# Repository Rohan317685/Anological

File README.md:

# Analogical 

This is Analogical; a project I've made for chipless.hackclub.com, The main goal of this project was to learn analog and not use a microcontroller! 

It is a 6 node transistor only signal network where each block drives, perturbs and destabalises the next creating a really chaotic annalog behaviour which cannot be replicated with a MCU

| Item                             | Item description                | Quantity | Price   | Link                                                                                                  |
|----------------------------------|---------------------------------|----------|---------|-------------------------------------------------------------------------------------------------------|
| PCB                              | Printed Circuit Board           | 5        | $5.5    | https://jlcpcb.com/                                                                                   |
| 10uF capacitor                   | for the led transistor          | 20       | $1.16   | https://www.lcsc.com/product-detail/C669099.html                                                      |
| 100nF capacitor                  | For decoupling                  | 50       | $1.07   | https://www.lcsc.com/product-detail/C89258.html                                                       |
| 10uF Electrolytic Capacitor      | For decoupling                  | 50       | $ 1.05  | https://www.lcsc.com/product-detail/C2841113.html                                                     |
| Red LED                          | For showing the patterns        | 20       | $ 0.73  | https://www.lcsc.com/product-detail/Light-Emitting-Diodes-LED_red_C99772.html                         |
| 1n41482 diode                    | For reverse polarity protection | 5        | $0.73   | https://www.lcsc.com/product-detail/C112342.html |
|  Pin header 1x2                  | For power supply                | 20        | $ 0.61  | https://www.lcsc.com/product-detail/C124375.html                                                      |
| Transistor JSCJ C1815 120~240-TA | For the transistors ofc         | 40       | $  1.04 | https://www.lcsc.com/product-detail/C382004.html                                                      |
| Resistor 100k                    | For resisting                   | 100      | $0.29   | https://www.lcsc.com/product-detail/C416061.html                                                      |
| Resistor 1k                      | For resisting aswell            | 100      | $ 0.42  | https://www.lcsc.com/product-detail/Chip-Resistor-Surface-Mount_1KR-1000-1_C95781.html                |
| AMS1117-3.3                      | Voltage regulator               | 5        | $ 0.99  | https://www.lcsc.com/product-detail/C6186.html                                                        |
|LCSC fees                         |Shipping/handling fees           | N/A      |$7.89    | lcsc.com                                                                                              |

I have used the cheapest shipping options and it comes to a total off: $22.48

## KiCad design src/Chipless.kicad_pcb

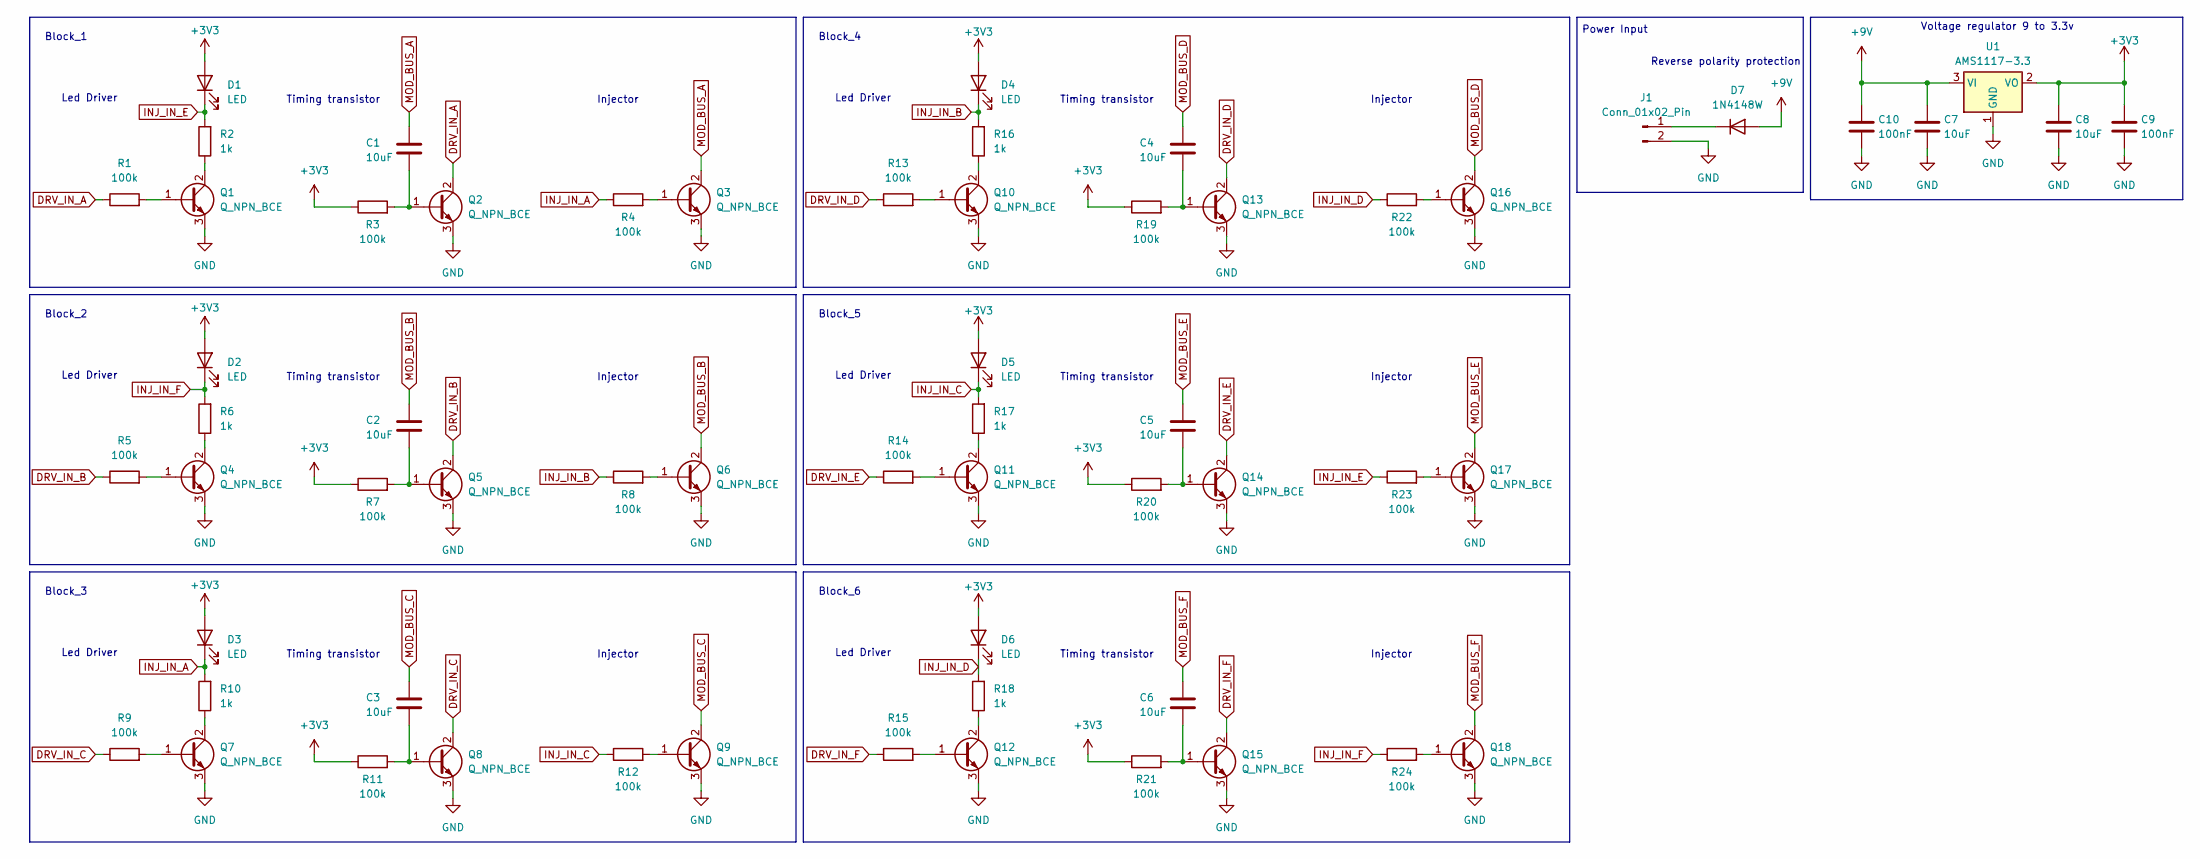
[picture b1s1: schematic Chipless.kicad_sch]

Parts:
C1, C2, C3, C4, C5, C6: 10uF; C_0805_2012Metric
C7, C8: 10uF; CP_Radial_D5.0mm_P2.00mm
C9, C10: 100nF; C_0805_2012Metric
D1, D2, D3, D4, D5, D6: LED; LED_D3.0mm
D7: 1N4148W; D_SOD-123
J1: Conn_01x02_Pin; PinHeader_1x02_P2.54mm_Vertical
Q1, Q2, Q3, Q4, Q5, Q6, Q7, Q8, Q9, Q10, Q11, Q12, Q13, Q14, Q15, Q16, Q17, Q18: Q_NPN_BCE; TO-92_Inline
R1, R3, R4, R5, R7, R8, R9, R11, R12, R13, R14, R15, R19, R20, R21, R22, R23, R24: 100k; R_0805_2012Metric
R2, R6, R10, R16, R17, R18: 1k; R_0805_2012Metric
U1: AMS1117-3.3; SOT-223-3_TabPin2

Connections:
+3V3: C8.1, C9.1, D1.2 (A), D2.2 (A), D3.2 (A), D4.2 (A), D5.2 (A), D6.2 (A), R3.1, R7.1, R11.1, R19.1, R20.1, R21.1, U1.2 (VO)
+9V: C7.1, C10.1, D7.2 (A), U1.3 (VI)
DRV_IN_A: Q2.2 (C), R1.1
DRV_IN_B: Q5.2 (C), R5.1
DRV_IN_C: Q8.2 (C), R9.1
DRV_IN_D: Q13.2 (C), R13.1
DRV_IN_E: Q14.2 (C), R14.1
DRV_IN_F: Q15.2 (C), R15.1
GND: C7.2, C8.2, C9.2, C10.2, J1.2, Q1.3 (E), Q2.3 (E), Q3.3 (E), Q4.3 (E), Q5.3 (E), Q6.3 (E), Q7.3 (E), Q8.3 (E), Q9.3 (E), Q10.3 (E), Q11.3 (E), Q12.3 (E), Q13.3 (E), Q14.3 (E), Q15.3 (E), Q16.3 (E), Q17.3 (E), Q18.3 (E), U1.1 (GND)
INJ_IN_A: D3.1 (K), R4.1, R10.2
INJ_IN_B: D4.1 (K), R8.1, R16.2
INJ_IN_C: D5.1 (K), R12.1, R17.2
INJ_IN_D: D6.1 (K), R18.2, R22.1
INJ_IN_E: D1.1 (K), R2.2, R23.1
INJ_IN_F: D2.1 (K), R6.2, R24.1
MOD_BUS_A: C1.1, Q3.2 (C)
MOD_BUS_B: C2.1, Q6.2 (C)
MOD_BUS_C: C3.1, Q9.2 (C)
MOD_BUS_D: C4.1, Q16.2 (C)
MOD_BUS_E: C5.1, Q17.2 (C)
MOD_BUS_F: C6.1, Q18.2 (C)
unnamed: D7.1 (K), J1.1
unnamed: Q1.1 (B), R1.2
unnamed: Q1.2 (C), R2.1
unnamed: C1.2, Q2.1 (B), R3.2
unnamed: Q3.1 (B), R4.2
unnamed: Q4.1 (B), R5.2
unnamed: Q4.2 (C), R6.1
unnamed: C2.2, Q5.1 (B), R7.2
unnamed: Q6.1 (B), R8.2
unnamed: Q7.1 (B), R9.2
unnamed: Q7.2 (C), R10.1
unnamed: C3.2, Q8.1 (B), R11.2
unnamed: Q9.1 (B), R12.2
unnamed: Q10.1 (B), R13.2
unnamed: Q10.2 (C), R16.1
unnamed: Q11.1 (B), R14.2
unnamed: Q11.2 (C), R17.1
unnamed: Q12.1 (B), R15.2
unnamed: Q12.2 (C), R18.1
unnamed: C4.2, Q13.1 (B), R19.2
unnamed: C5.2, Q14.1 (B), R20.2
unnamed: C6.2, Q15.1 (B), R21.2
unnamed: Q16.1 (B), R22.2
unnamed: Q17.1 (B), R23.2
unnamed: Q18.1 (B), R24.2

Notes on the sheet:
Led Driver
Block_3
Reverse polarity protection
Block_6
Voltage regulator 9 to 3.3v
Power Input
Timing transistor
Block_2
Injector
Block_1
Block_5
Block_4

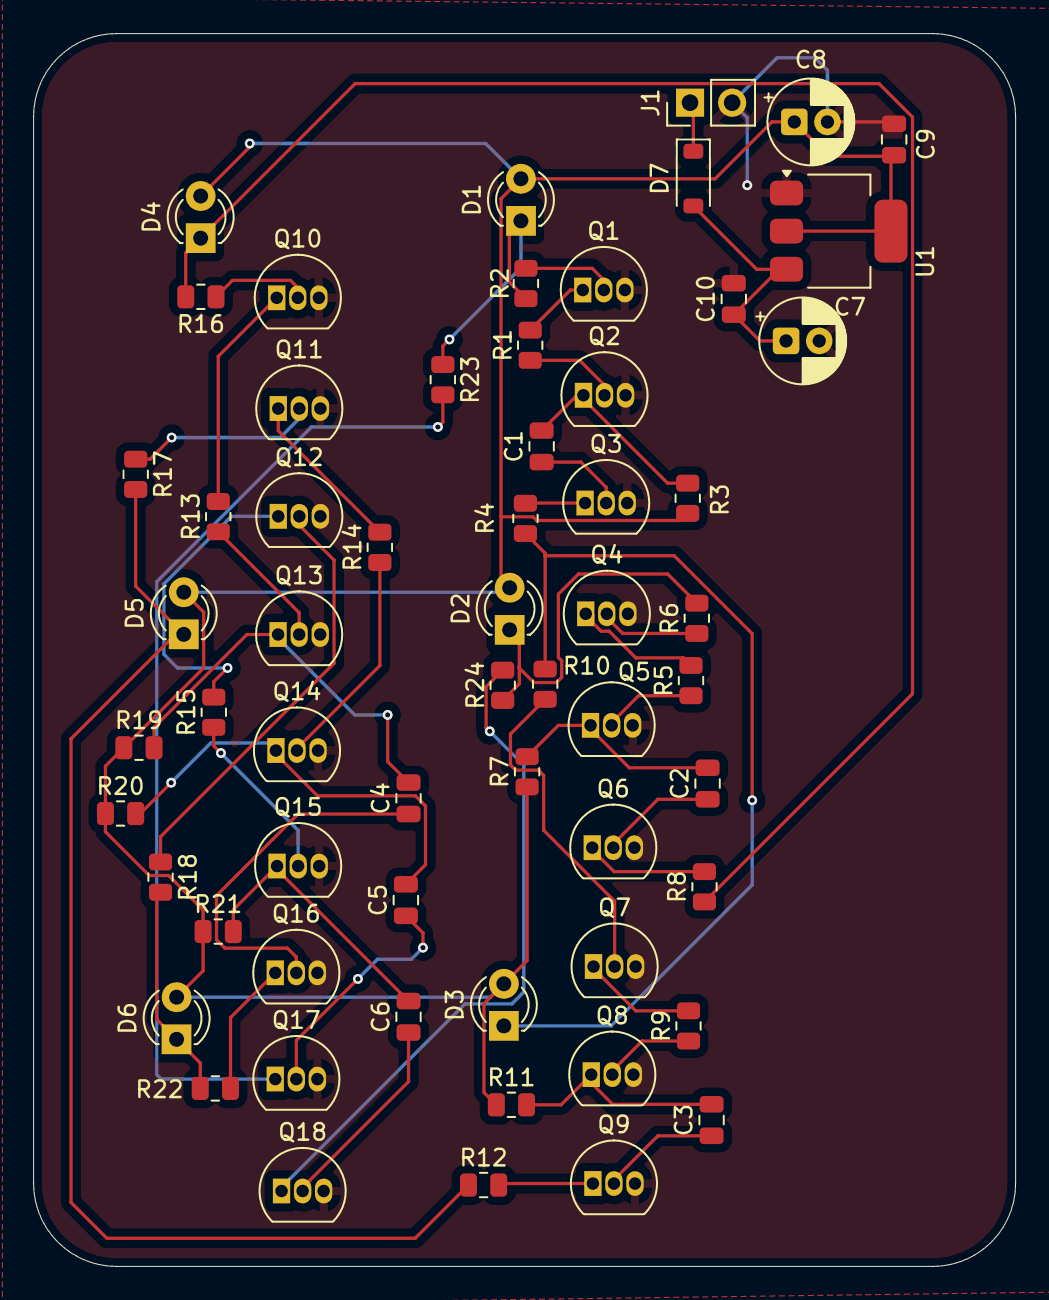
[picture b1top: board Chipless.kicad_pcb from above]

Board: 2 copper layers, 59.2 x 74.4 mm, 61 parts (0 on the bottom side), 46 nets.

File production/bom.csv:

Designator,Footprint,Quantity,Value,LCSC Part #
"C1, C2, C3, C4, C5, C6",0805,6,10uF,
"C10, C9",0805,2,100nF,
"C7, C8",CP_Radial_D5.0mm_P2.00mm,2,10uF,
"D1, D2, D3, D4, D5, D6",LED_D3.0mm,6,LED,
D7,D_SOD-123,1,1N4148W,
J1,PinHeader_1x02_P2.54mm_Vertical,1,Conn_01x02_Pin,
"Q1, Q10, Q11, Q12, Q13, Q14, Q15, Q16, Q17, Q18, Q2, Q3, Q4, Q5, Q6, Q7, Q8, Q9",TO-92_Inline,18,Q_NPN_BCE,
"R1, R11, R12, R13, R14, R15, R19, R20, R21, R22, R23, R24, R3, R4, R5, R7, R8, R9",0805,18,100k,
"R10, R16, R17, R18, R2, R6",0805,6,1k,
U1,SOT-223-3_TabPin2,1,AMS1117-3.3,

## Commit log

2026-06-20 quick bom without some info will update after lunch
